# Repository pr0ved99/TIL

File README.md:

# TIL (Today I Learned)
"**2026년 상반기 목표**: AI 의존도를 낮추고 데이터시트 기반의 기술 자립을 이룬다.
(Current Status: Zero to One)"

<div align="center">
  <h3>🚀 Lee YeongHyeon's Tech Archive</h3>
  <p>삼성 청년 SW 아카데미(SSAFY) 임베디드 로봇 트랙에서 공부한 기록입니다.</p>
</div>

<div align="center">

</div>

---

## 📂 Category & Contents
공부한 지식들을 체계적으로 분류하여 관리합니다.

| 카테고리 | 상세 내용 |
| :--- | :--- |
| **💻 Language** | C, C++, Python 핵심 문법 및 고급 기법 |
| **🔌 Embedded** | [STM32(NUCLEO-F446RE)](./Embedded/STM32), [CAN](./Embedded/STM32/CAN), [FreeRTOS](./Embedded/STM32/RTOS), Raspberry Pi 5, Linux 환경 설정 |
| **🤖 Robotics** | [ROS 2 Humble](./Robotics/ROS2), [VSLAM](./Robotics/VSLAM), SLAM, Kinematics, URDF 모델링 |
| **🧠 CS 기초** | Git 컨벤션, 네트워크, OS 원리 |

---

## 📝 Algorithm Study
알고리즘 문제 풀이와 구현 연습은 전용 저장소에서 더욱 밀도 있게 관리하고 있습니다.

> **[Daily Algorithm Repository 바로가기](https://github.com/pr0ved99/daily-algorithm)** > *이곳(TIL)에는 핵심 알고리즘 이론과 오답 노트만 기록합니다.*

---

## 📊 GitHub Stats
<div align="center">

</div>

---

## 💡 My Principles
- **매일 조금씩이라도 기록하기**: 망각하기 전에 내 언어로 정리한다.
- **Why에 집중하기**: 단순 코드가 아닌, 동작 원리와 이유를 파헤친다.
- **공유의 가치**: 누군가에게 도움이 될 수 있는 퀄리티로 작성한다.

<div align="center">
  <p>Copyright © 2026 Lee YeongHyeon. All rights reserved.</p>
</div>

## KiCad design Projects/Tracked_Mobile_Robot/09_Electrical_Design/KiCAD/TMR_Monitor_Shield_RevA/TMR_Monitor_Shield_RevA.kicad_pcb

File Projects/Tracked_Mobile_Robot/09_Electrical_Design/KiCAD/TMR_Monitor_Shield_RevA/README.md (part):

# TMR Monitor Shield RevA — 노트북 설계 시작점

**현재 · 2026-11-12:** [기본 경로의 최신 회로도 PDF](exports/TMR_Monitor_Shield_RevA_schematic.pdf)를 현재 저장 회로도에서 다시 생성했다. 40부품과 PWR_FLAG 2개, J7/J8을 포함한 6개 측정 포트가 반영되어 있다. 왼쪽 아래 `04 VOLTAGE INPUTS – TWO CHANNELS` 영역의 위쪽은 J7/VBAT_SENSE, 아래쪽은 J8/VMOTOR_SENSE다. 11/7 게시본과 본문·렌더링이 일치하며 CAD 원본은 변경하지 않았다. [확인 기록](../../../assets/logs/pcb_design/2026-11-12_export_sync/README.md).

11/13에41-1~41-5 자료 및 기본 exports/reports 최신화를 마감한다. 현재 필기/질문 뒤41-6 보호 경로·검증 기준으로 이어간다. 실물/ADC 검증 완료가 아니다. 회로도 변경 뒤에는 위 고정 경로의 PDF도 함께 갱신한다. 날짜별 검토 로그는 당시 기록으로 보존한다. 아래 재개점은 각 날짜의 이력이다.

**현재 재개점 · 2026-11-07:**

전압2채널·공통 제어와PWR_FLAG2개까지 사용자 작성 완료,40부품·활성22net·기존 설정 ERC0/0이다. Codex가 마감 시 오래된 주석/제목란만 갱신했다. [최신 PDF·검증](../../../assets/logs/pcb_design/2026-11-07_cad_closeout/README.md). 다음은 수집·필터 표와 포트·전원 조건표이며 풋프린트/기구·PCB는 그 뒤다. 후보 BOM은40부품으로 갱신했으나 구매/제작 승인은 아니다. 아래는 당시 이력이다.

**현재 재개점 · 2026-11-06:** TPS=U1·TMUX=U2 추가 후 [24부품을6영역으로 재배치](../../../assets/logs/pcb_design/2026-11-06_schematic_layout_review/README.md)했다. 이후 사용자가 배터리측 J7/R7~R11/C5를 배치해 **현재31부품**이다. J7 위100mil·R9/C5 아래300mil 이동을 실제 저장 파일에서 확인했다. [최신 배치 PDF·검토](../../../assets/logs/pcb_design/2026-11-06_voltage_upstream_placement/README.md). 다음은 사용자가 **전단 분압·필터 배선**→모터 공급측/공통→연결 대조/ERC 순으로 진행한다. [설계27 연결표](../../27_Voltage_2Ch_Schematic_Contract_Comparison_2026-11-06_ko.md)를 따른다. 새7부품14핀과 U1/U2의19핀은 미배선이고 모터 공급측 전압 채널·C7/C8은 미추가다. 활성10net·기존 X70개를 유지한다. 이 쉴드의 새ERC/DRC·PCB 편집은 미실행이며 풋프린트/TI 예시 패드 차이는 후속 검토다. 별도로 수행한 MVP RevB 정돈/ERC와 구분한다. [오늘 진행](../../../docs/progress/2026-11-06_progress.md). 아래 다음 작업은 당시 이력이다.

**이전 재개점 · 2026-10-29:** [학습 노트20](../../../07_Embedded_Learning_Notes/01_Concept_Notes/20_KiCad_Current_NTC_Voltage_Simulation_Lab_ko.md) · [설계 판단24](../../24_Monitoring_Input_Simulation_and_Design_Review_2026-10-28_ko.md) · [실습 원본](../Simulation/README.md). 전류 RC AC/TRAN·NTC25/50°C 상당 OP/AC·전압 분압12.6/16V OP와 AC의 사용자 GUI 실습 및 PNG/CSV 저장을 완료했다. 전압 fc404.942Hz·저주파−15.7157dB·차단점−18.7260dB, NTC VDD(CN7-5) 공급 기본안은 실제 쉴드 미반영이다. 기존22부품/미배선32개쉴드와시뮬레이션회로를구분한다. 다음은 **전압 채널 ±0.10V 목표의 저항 공차·VDDA·ADC/보호 누설·보정 오차 예산 → 정상/고장/무전원 보호 조건 → 준비된 실제 쉴드 변경 검토**다. 아래날짜별다음작업은당시이력이다.

**이전 재개점 · 2026-10-27:** [전류 검증 명세22](../../22_Current_Channel_Verification_Spec_2026-10-27_ko.md)와 [온도 검증 명세23](../../23_Temperature_Channel_Verification_Spec_2026-10-27_ko.md)를 작성했다. 전류 입력계4.4mV·온도 입력계1°C를 시험용 기준으로, 비교 경계·보정/독립점·절차·장비 적합성을 구체화했다. RT 표 환산을 시험 기준으로 사용하고 RC는 비교 대상으로 유지한다. 실물 NOT_RUN·제작용 아님. 다음은 NTC 여기/ADC 기준·무전원 보호의 미결과 전압2채널 설계다. 아래 날짜별3-1 재개 표기는 당시 이력이며 반복 지시가 아니다.

**10/27 외부 설계 비교:** [유사 프로젝트 평가](../../21_External_Project_Monitoring_Architecture_Review_2026-10-27_ko.md)에서 Waveshare·ODrive·VESC의 측정 위치/부품/선정 이유를 비교했다. 현 방향은 타당하나 전압2·전원/보호 결정과 한 채널 검증이 필요하다. 기존 후보·CAD·실측 NOT_RUN은 유지하며, 아래3-1 학습 재개에 연결하는 권고다.

**학습 자료 이력 · 2026-10-26 마감:** [학습 목차](../../../07_Embedded_Learning_Notes/01_Concept_Notes/README.md)에 2장 추가 자료와 **3-1~3-4 검증 학습 노트 네 편**을 작성했다. 다음은 3-1부터 함께 읽기와 목표/오차 배분/계기·연결 조건의 미정 검토다. 12kΩ/100nF·14MHz/480cycles·NTC STM 공급 B안은 후보,100Hz·10개 평균은 첫 DC 비교 제안이다. 실물 시험 NOT_RUN, 요구 채택·부품 확정·CAD/BOM/펌웨어 변경 없음. [마감 근거](../../../docs/progress/2026-10-26_progress.md). 아래 날짜별 “다음”은 당시 이력이다.

2026-10-23. **RevA.0 초안 / 회로도·초기 부품 배치 / 미배선 / 제작용 아님**.

**2단계 종합 검토본:** [ADC6채널 연결·측정 기준](../../20_Analog_6Ch_Contract_and_Stage2_Review_2026-10-23_ko.md). PC0/1 전류·PC2/3 온도·PA4/PB0 전압의 포트/핀 순서를 모았다. 전류센서 nonratiometric·NTC VEXC/VDDA 비율·미분압 rail 보호를 구분했다. 구성 검토본 작성 완료이며 승인/실측 PASS는 아니다. 당시 다음 작업이었던 ADC 기준·NTC 여기·무전원 경로 비교/계산은 아래 10/24 검토에 기록했다. 현재 다음 작업은 상단 최신 재개점을 따른다.

**CAN 연결 계약 초안:** [GPIO·커넥터 검토](../../19_CAN_GPIO_and_Connector_Contract_2026-10-23_ko.md). ESP GPIO4 TX/GPIO5 RX와 ESP 가까운 트랜시버 배치를 제안했다. 별도3.3V 전원·논리3선·버스3선,2/3노드 종단 전환을 기록했다. 기존 UART17/18 유지, HG 실물/전원 OFF 보호·커넥터 제품/키는 미확정. 다음은 ADC6채널 포트/기준 계약과2단계 종합 검토다.

**전원 구조 검토안:** [3.3V 공급·조립 검토](../../18_Expansion_3V3_Supply_Structure_and_Assembly_2026-10-23_ko.md). #2 병렬 분기→단일 LDO→센서/CAN 분배와 TO-220급을 우선 제안한다. 출력 오차 포함 발열 사례0.615W, MCP1825S는 ±2.5%로 초기±1% 탐색 조건에 미달하여 미선정. 무전원 역급전·NTC 기준·#2 전체 여유는 OPEN이다. 다음은 ESP GPIO/커넥터 계약이며 CAD/BOM은 유지한다.

**채택한 목표:** STM 센서/구동 집중 + ESP Wi-Fi–CAN 게이트웨이 + 개발용 CANable. 별도 센서 MCU 추가 없음. 두 MCU용 트랜시버와 각 노드의 전원/핀/배치를 검토한다. 최신 확장 전원은 XL4015 #2 AUX5V 병렬 분기 → 별도3.3V 생성안이다. 추가 부하235mA/연속 설계300mA·LDO 손실약0.51~0.59W 계산안을 검토하며 실제 품번·방열·#2 전체 공급 여유는 미확정이다. [전원 예산 계산](../../17_Expansion_Power_Budget_2026-10-23_ko.md).

**현재 작업은3단계 입력 회로 상세 검토다.** NTC와 전류 RC·ADC 획득·수집 주기·평균·보정 후 오차 예산과 검증 학습 자료를 정리했다. 요구 채택·시험 조건 확정과 실측·부품 확정은 남았다.2단계 계약은20번 문서의 검토본이며 아래 CAD의 실제 전원·커넥터 순서는 아직 이전 초안이다.

이번 회차는 노트북만으로 설계 학습 자료를 정리했고 10/26 마감한다. 다음 물리 작업 시각은 지정하지 않았다. NUCLEO-F446RE 상면 확장 쉴드를 검토하며, **현재 CAD에는 전류 2채널·온도 2채널의 센서 부분만 작성되어 있다. 전체 확장 기능을 반영한 설계가 아니다.** 이 보드 완성은 현재 MVP의 새 선행 조건이 아니다.

## 전체 기능 범위 재대조 — 2026-10-23

사용자가 CAN·향후 LiDAR까지 고려하도록 요청했고, **IMU는 기존 만능기판에 이미 자리를 배치했음**을 재확인했다. 센서 4채널만으로 범위를 좁힌 초기 안내를 정정한다. 기존 기판을 유지하면서 아래 기능을 검토하며, 이번 범위 대조로 CAD 회로나 BOM에 부품을 추가한 것은 아니다.

| 기능 | 새 PCB에서의 처리 | 현재 근거·남은 결정 |
| --- | --- | --- |
| 좌우 모터 전류 2채널 | 외부 #5241의 전원·출력 신호 접속, 입력 필터·보호 | PC0/PC1 초안 있음. 모터 전류가 통과하는 센서 주전류 단자·배선은 외부 유지 |
| 좌우 모터 온도 2채널 | 외부 NTC 접속, 분압·필터·보호 | PC2/PC3 초안 있음. 보호·단선 판정·실물 부품 대조 미완료 |
| **K1 전단·후단 전압 2채널** | 분압·필터·보호·측정점 추가 설계 대상 | PA4/PB0 기존 예약. 현재 CAD에는 없음. 상류 `VBAT_PROTECTED_SENSE`와 하류 `MOTOR_VBAT_SAFE_SENSE` 구분 |
| **CAN** | 트랜시버 접속, CANH/CANL/GND 커넥터, 종단 선택·디커플링·보호 검토 | PA12 TX/PA11 RX 예약. 보유 MCU-230 활용 우선 검토; 실제 단자·크기·RS·내장 종단 미확인. 현재 CAD에는 없음 |
| IMU | **기존 만능기판 위치·배선 유지. 새 PCB에 중복 실장하지 않음** | PB8/PB9 I2C, PB1 INT, PC4 RESET 보존. 기존 JDBG 접근·상면 간섭만 검토. 새 IMU 커넥터도 기본 추가 대상이 아님 |
| 로직 전원·유지보수 | 센서와 CAN을 포함한 3.3V 부하 예산, 전원 디커플링·입력 보호·역급전 경로, 전원/신호 시험점 검토 | 기존 XL4015 전원 경계와 USB 전환 정책 유지. 기존 UART/엔코더/제어/SWD/RESET 접근 보존; 모든 신호의 커넥터 중복 추가는 불필요 |
| 향후 LiDAR·상위 컴퓨터 | 모델 선정 전까지 필요한 전원·데이터 연결 조건과 하네스 통로를 미결 항목으로 관리 | 별도 장착이 기존 방향. 공급 전압·정상/기동 전류·USB/UART/Ethernet 등 실제 인터페이스·커넥터가 정해진 뒤 PCB 포함 여부 결정. 지금 레귤레이터·USB 허브·레벨 변환기를 임의로 추가하지 않음 |
| 예비 확장 | 기존 핀 예약과 물리 접근성 보존 | PA6/PA7 추가 ADC 후보, PC5/PC6 선택적 gate/brake 예약. 현재 필수 회로나 확정 커넥터로 승격하지 않음 |

따라서 기존 계획을 합치면 **아날로그 6채널(전류 2 + 온도 2 + 전압 2)과 CAN**이 새 확장 PCB의 주요 검토 범위다. 전단 전압 입력을 배터리 상태 관측에도 활용하는 안이므로 별도 배터리 ADC를 자동으로 더해 7채널로 세지 않는다. 현재 리포 알람의 사용자 보고 검증과 앞으로 구현할 ADC 측정은 별개다.

CANable V2.0 Pro는 보유한 **PC 측 USB-CAN 장치**다. 새 PCB 실장 부품이나 추가 구매 대상으로 세지 않는다. CAN 종단은 물리 버스 양 끝의 120Ω 구성을 기준으로 하되, 보유 모듈의 내장 종단부터 확인해 중복 추가를 피한다. LiDAR 데이터 경로는 해당 모델과 상위 ROS 2 컴퓨터의 연결을 별도로 정하며, CAN 포트가 LiDAR 데이터 포트를 대신한다고 가정하지 않는다.

MDD10A·XL4015·K1·버스바·퓨즈·배터리는 기존 별도 전력 구역을 유지한다. 엔코더 조정부, PWM/DIR 풀다운, E-stop 감지와 ESP32 UART 회로도 기존 기판에 남긴다. 새 PCB의 부품 수와 면적은 이 경계를 기준으로 산정한다.

근거: [전체 확장 배치 검토](../../13_Two_Deck_Perfboard_Expansion_Feasibility_2026-09-30_ko.md), [전압 ADC 공간 검토](../../12_Dual_Rail_ADC_Space_Review_2026-09-30_ko.md), [현재 핀 배정과 IMU 배선 이력](../../../01_System_Architecture/06_MCU_Pin_Allocation_Candidate_ko.md), [CAN 통합 계획·보유 장비](../../../01_System_Architecture/14_CAN_Bus_Integration_Plan_ko.md). 과거 하층 만능기판의 면적 예산은 현재 상면 쉴드의 수용 가능성 증거가 아니므로 새로 배치 검토한다.

## 열 파일과 현재 결과

1. [KiCad 프로젝트](TMR_Monitor_Shield_RevA.kicad_pro)를 연다.
2. [회로도](TMR_Monitor_Shield_RevA.kicad_sch)를 먼저 보고, [PCB](TMR_Monitor_Shield_RevA.kicad_pcb)에서 배치를 확인한다.
3. 편집 없이 확인하려면 [최신 회로도 PDF](exports/TMR_Monitor_Shield_RevA_schematic.pdf)를 사용한다. [PCB 초기 배치 PDF](exports/TMR_Monitor_Shield_RevA_placement.pdf)는 22풋프린트 초안으로, 최신 회로도의 40부품이 모두 반영된 배치도가 아니다.

[부품 후보 CSV](bom_candidates.csv)는 풋프린트 대조용이며 구매·제작 BOM이 아니다.

| 산출물 | 현재 범위 |
| --- | --- |
| 회로도 | Morpho 암 소켓 2개, 외부 측정 커넥터 6개, 저항 16개, 커패시터 8개, IC 2개, 시험점 6개: 총 40부품. PWR_FLAG 2개 별도 |
| PCB | 부품 22개 배치, 구리 배선/영역 0개. 연결선 32개 미배선 |
| ERC | 11/12 새 추출: 40부품 회로도 오류 0/경고 0, 기존 무시 규칙 4개 유지 |
| DRC | 11/12 저장 PCB 검사: 배치 위반 0, 회로도 대조 21건(미반영 부품18 + net 충돌3), 미배선32. **전체 DRC PASS가 아님** |
| 연결 대조 | 11/12 저장 회로도 추출 결과 전체 91net(활성 22개 포함), 11/7 게시본과 동일. 헤더·외부 포트 활성 핀 23개를 대조 |

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
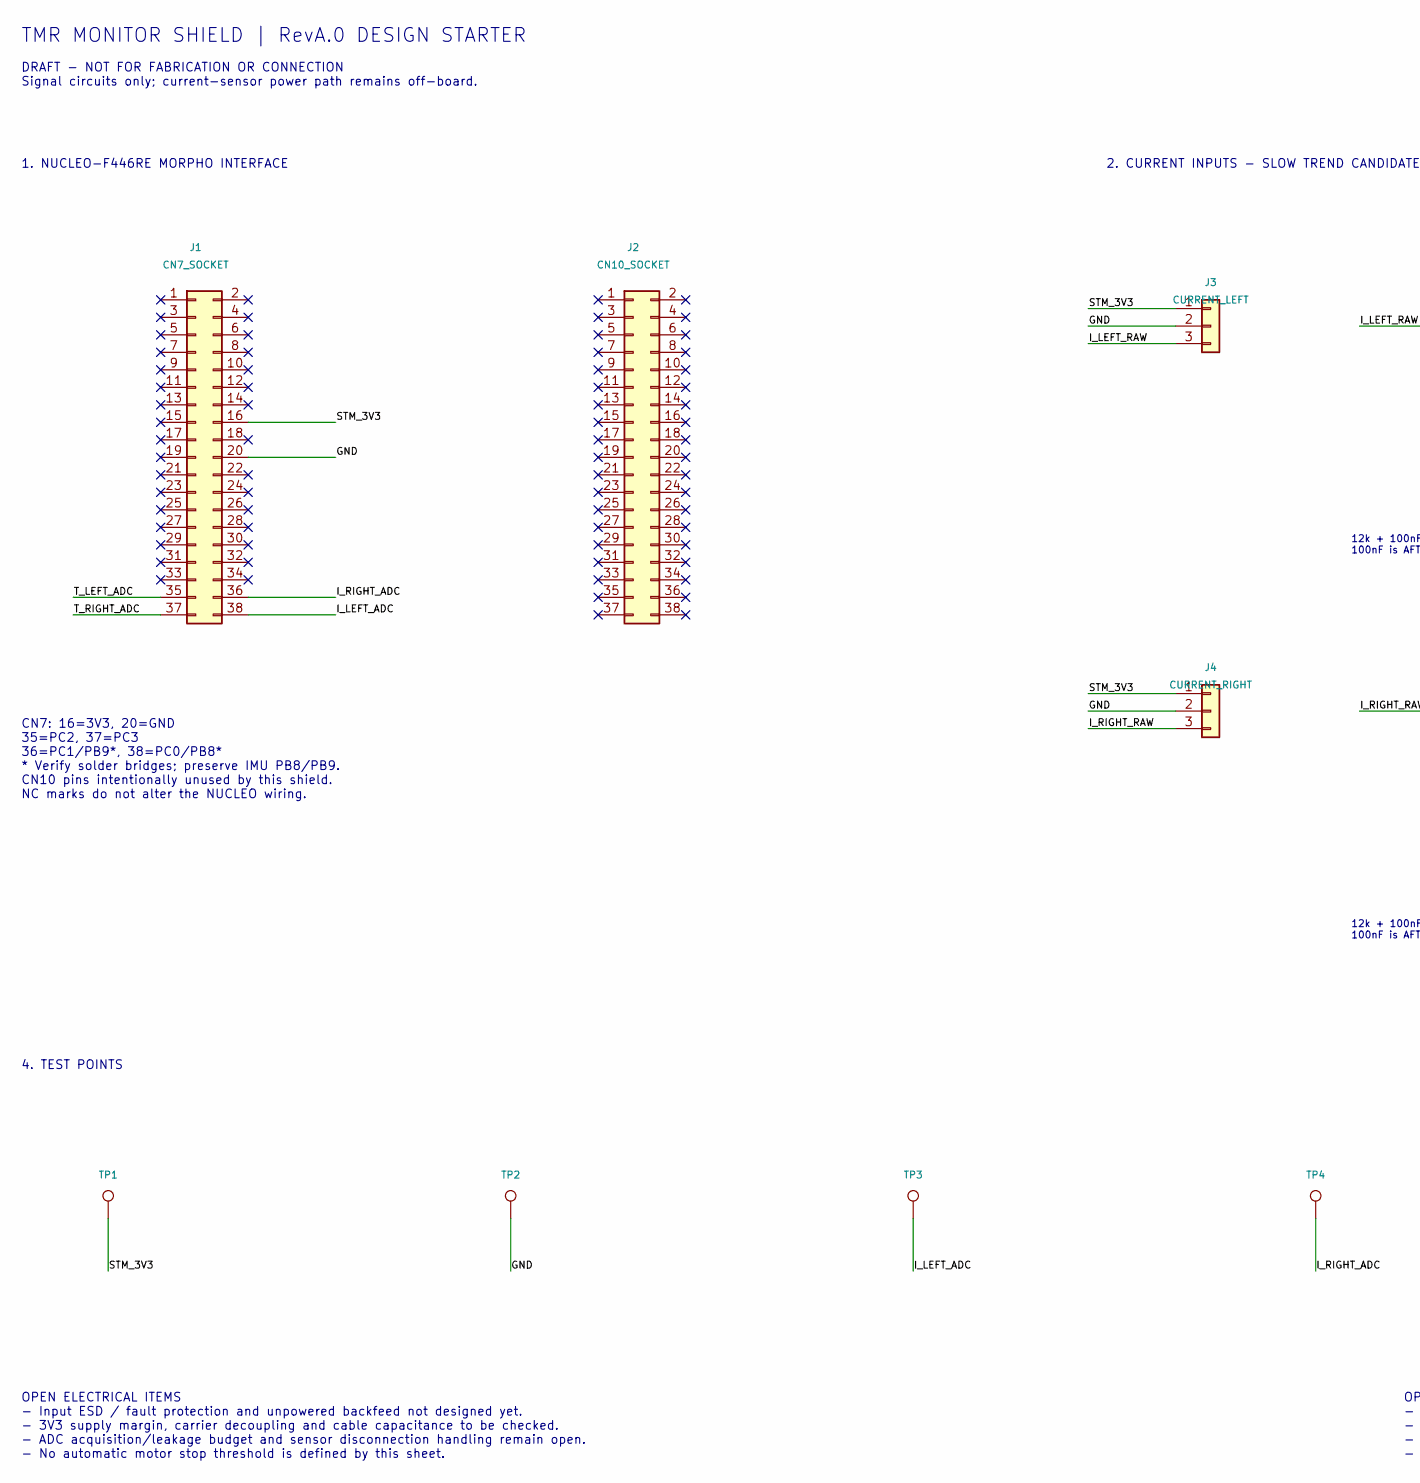
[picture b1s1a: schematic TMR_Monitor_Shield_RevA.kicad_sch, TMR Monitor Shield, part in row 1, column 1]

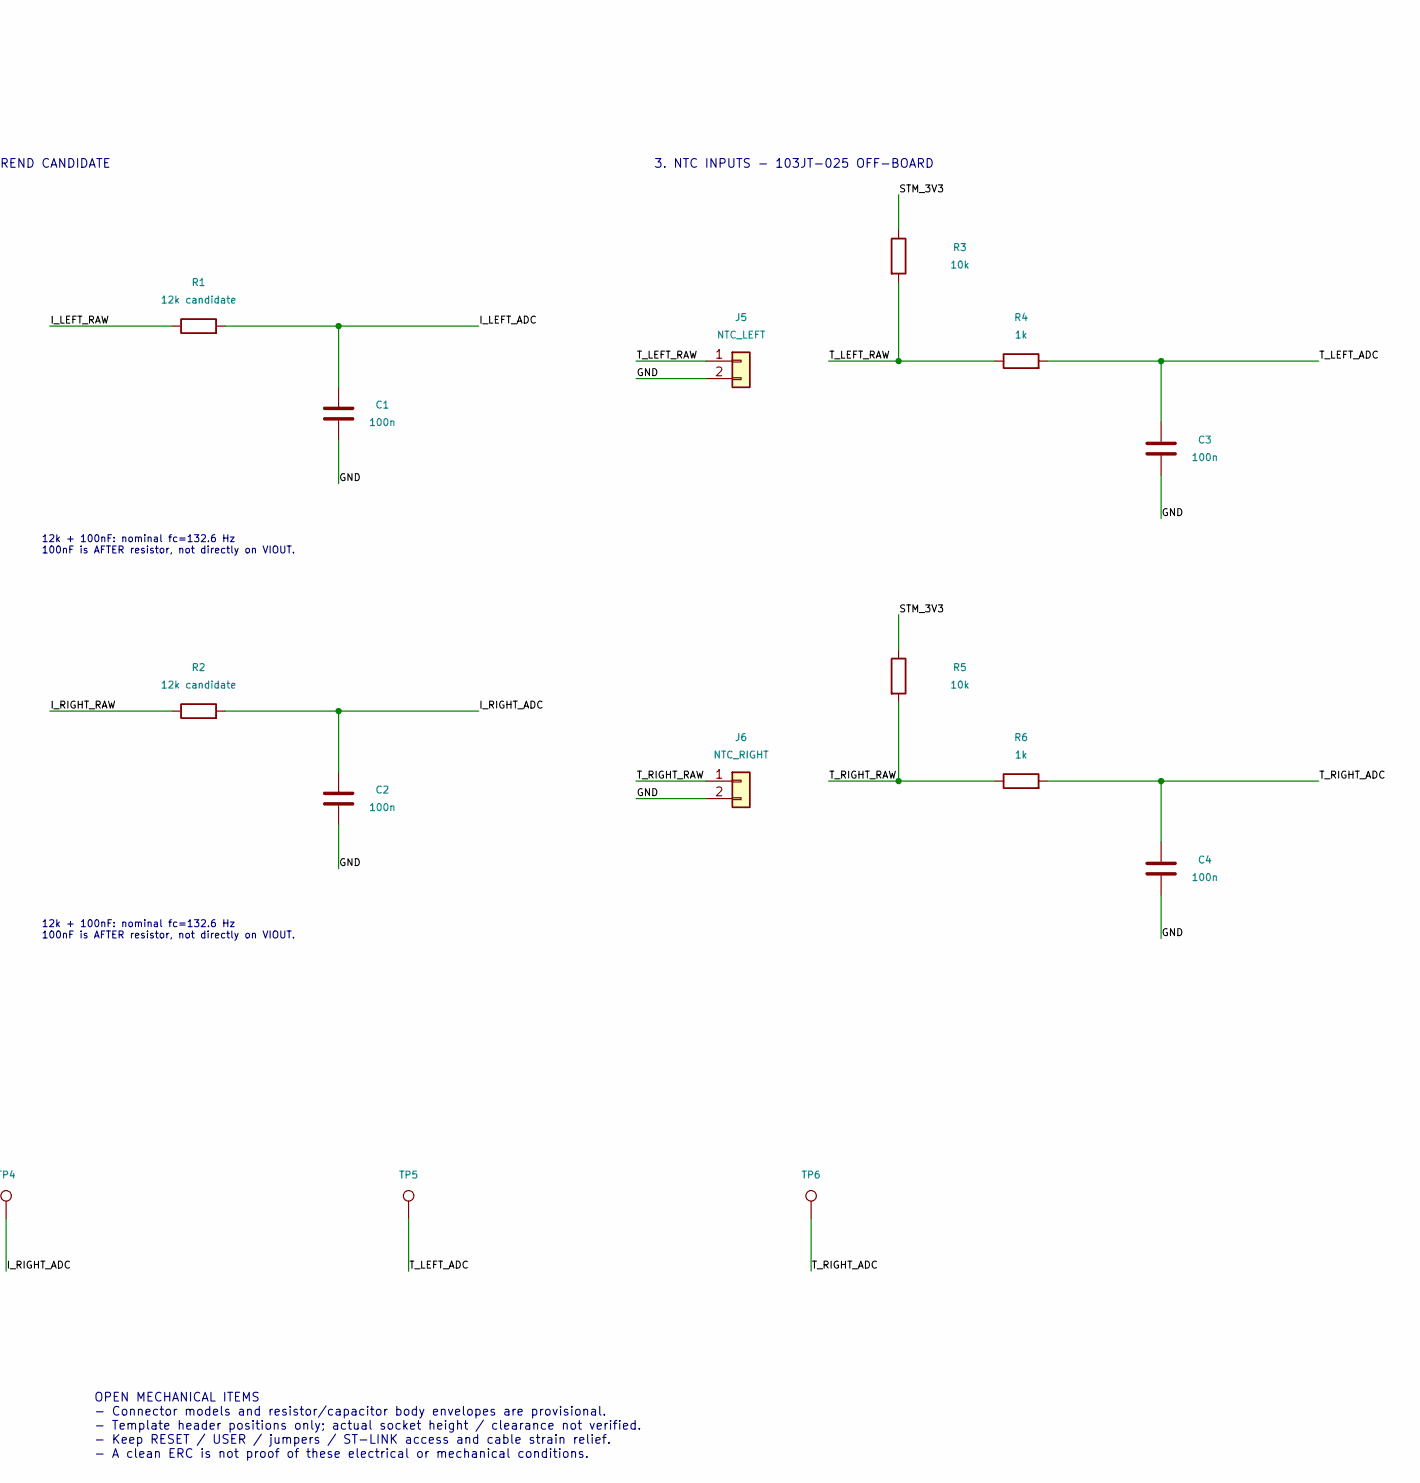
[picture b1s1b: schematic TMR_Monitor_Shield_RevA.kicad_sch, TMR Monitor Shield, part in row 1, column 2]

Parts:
C1, C2, C3, C4: 100n; C_Disc_D5.0mm_W2.5mm_P5.00mm
J1: CN7_SOCKET; PinSocket_2x19_P2.54mm_Vertical
J2: CN10_SOCKET; PinSocket_2x19_P2.54mm_Vertical
J3: CURRENT_LEFT; JST_XH_B3B-XH-A_1x03_P2.50mm_Vertical
J4: CURRENT_RIGHT; JST_XH_B3B-XH-A_1x03_P2.50mm_Vertical
J5: NTC_LEFT; JST_XH_B2B-XH-A_1x02_P2.50mm_Vertical
J6: NTC_RIGHT; JST_XH_B2B-XH-A_1x02_P2.50mm_Vertical
R1, R2: 12k candidate; R_Axial_DIN0207_L6.3mm_D2.5mm_P7.62mm_Horizontal
R3, R5: 10k; R_Axial_DIN0207_L6.3mm_D2.5mm_P7.62mm_Horizontal
R4, R6: 1k; R_Axial_DIN0207_L6.3mm_D2.5mm_P7.62mm_Horizontal
TP1: STM_3V3; TestPoint_THTPad_D1.5mm_Drill0.7mm
TP2: GND; TestPoint_THTPad_D1.5mm_Drill0.7mm
TP3: I_LEFT_ADC; TestPoint_THTPad_D1.5mm_Drill0.7mm
TP4: I_RIGHT_ADC; TestPoint_THTPad_D1.5mm_Drill0.7mm
TP5: T_LEFT_ADC; TestPoint_THTPad_D1.5mm_Drill0.7mm
TP6: T_RIGHT_ADC; TestPoint_THTPad_D1.5mm_Drill0.7mm

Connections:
/GND: C1.2, C2.2, C3.2, C4.2, J1.20, J3.2, J4.2, J5.2, J6.2, TP2.1
/I_LEFT_ADC: C1.1, J1.38, R1.2, TP3.1
/I_LEFT_RAW: J3.3, R1.1
/I_RIGHT_ADC: C2.1, J1.36, R2.2, TP4.1
/I_RIGHT_RAW: J4.3, R2.1
/STM_3V3: J1.16, J3.1, J4.1, R3.1, R5.1, TP1.1
/T_LEFT_ADC: C3.1, J1.35, R4.2, TP5.1
/T_LEFT_RAW: J5.1, R3.2, R4.1
/T_RIGHT_ADC: C4.1, J1.37, R6.2, TP6.1
/T_RIGHT_RAW: J6.1, R5.2, R6.1

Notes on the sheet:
TMR MONITOR SHIELD | RevA.0 DESIGN STARTER
DRAFT - NOT FOR FABRICATION OR CONNECTION Signal circuits only; current-sensor power path remains off-board.
1. NUCLEO-F446RE MORPHO INTERFACE
CN7: 16=3V3, 20=GND 35=PC2, 37=PC3 36=PC1/PB9*, 38=PC0/PB8* * Verify solder bridges; preserve IMU PB8/PB9. CN10 pins intentionally unused by this shield. NC marks do not alter the NUCLEO wiring.
2. CURRENT INPUTS - SLOW TREND CANDIDATE
12k + 100nF: nominal fc=132.6 Hz 100nF is AFTER resistor, not directly on VIOUT.
3. NTC INPUTS - 103JT-025 OFF-BOARD
4. TEST POINTS
OPEN ELECTRICAL ITEMS - Input ESD / fault protection and unpowered backfeed not designed yet. - 3V3 supply margin, carrier decoupling and cable capacitance to be checked. - ADC acquisition/leakage budget and sensor disconnection handling remain open. - No automatic motor stop threshold is defined b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
OPEN MECHANICAL ITEMS - Connector models and resistor/capacitor body envelopes are provisional. - Template header positions only; actual socket height / clearance not verified. - Keep RESET / USER / jumpers / ST-LINK access and cable strain relief. - A clean ERC is not proof of these electrical or 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

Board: 2 copper layers, 22 parts (2 on the bottom side), 10 nets, no tracks yet.

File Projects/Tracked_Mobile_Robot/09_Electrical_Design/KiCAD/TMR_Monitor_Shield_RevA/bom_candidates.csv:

Reference,Value,Footprint_candidate,Status,Notes
J1,CN7_SOCKET,Connector_PinSocket_2.54mm:PinSocket_2x19_P2.54mm_Vertical,CANDIDATE_NOT_PURCHASE_ORDER,Bottom female socket; height and mating geometry to be checked
J2,CN10_SOCKET,Connector_PinSocket_2.54mm:PinSocket_2x19_P2.54mm_Vertical,CANDIDATE_NOT_PURCHASE_ORDER,Bottom female socket; height and mating geometry to be checked
J3,CURRENT_LEFT,Connector_JST:JST_XH_B3B-XH-A_1x03_P2.50mm_Vertical,CANDIDATE_NOT_PURCHASE_ORDER,"JST-XH 3-pin candidate, not purchased or verified; 1=3V3 2=GND 3=VIOUT"
R1,12k candidate,Resistor_THT:R_Axial_DIN0207_L6.3mm_D2.5mm_P7.62mm_Horizontal,VALUE_OWNED_BODY_TOLERANCE_NOT_VERIFIED,Output isolation / RC; value and lead spacing remain provisional
C1,100n,Capacitor_THT:C_Disc_D5.0mm_W2.5mm_P5.00mm,PART_PURCHASED_BODY_FOOTPRINT_NOT_VERIFIED,Vishay K104K15X7RF53H5 purchased; generic body envelope remains provisional
J4,CURRENT_RIGHT,Connector_JST:JST_XH_B3B-XH-A_1x03_P2.50mm_Vertical,CANDIDATE_NOT_PURCHASE_ORDER,"JST-XH 3-pin candidate, not purchased or verified; 1=3V3 2=GND 3=VIOUT"
R2,12k candidate,Resistor_THT:R_Axial_DIN0207_L6.3mm_D2.5mm_P7.62mm_Horizontal,VALUE_OWNED_BODY_TOLERANCE_NOT_VERIFIED,Output isolation / RC; value and lead spacing remain provisional
C2,100n,Capacitor_THT:C_Disc_D5.0mm_W2.5mm_P5.00mm,PART_PURCHASED_BODY_FOOTPRINT_NOT_VERIFIED,Vishay K104K15X7RF53H5 purchased; generic body envelope remains provisional
J5,NTC_LEFT,Connector_JST:JST_XH_B2B-XH-A_1x02_P2.50mm_Vertical,CANDIDATE_NOT_PURCHASE_ORDER,JST-XH 2-pin candidate; 1=NTC node 2=GND; external 103JT-025
R3,10k,Resistor_THT:R_Axial_DIN0207_L6.3mm_D2.5mm_P7.62mm_Horizontal,VALUE_OWNED_BODY_TOLERANCE_NOT_VERIFIED,NTC divider; actual resistance/tolerance and body size unconfirmed
R4,1k,Resistor_THT:R_Axial_DIN0207_L6.3mm_D2.5mm_P7.62mm_Horizontal,VALUE_OWNED_BODY_TOLERANCE_NOT_VERIFIED,Draft component
C3,100n,Capacitor_THT:C_Disc_D5.0mm_W2.5mm_P5.00mm,PART_PURCHASED_BODY_FOOTPRINT_NOT_VERIFIED,Vishay K104K15X7RF53H5 purchased; generic body envelope remains provisional
J6,NTC_RIGHT,Connector_JST:JST_XH_B2B-XH-A_1x02_P2.50mm_Vertical,CANDIDATE_NOT_PURCHASE_ORDER,JST-XH 2-pin candidate; 1=NTC node 2=GND; external 103JT-025
R5,10k,Resistor_THT:R_Axial_DIN0207_L6.3mm_D2.5mm_P7.62mm_Horizontal,VALUE_OWNED_BODY_TOLERANCE_NOT_VERIFIED,NTC divider; actual resistance/tolerance and body size unconfirmed
R6,1k,Resistor_THT:R_Axial_DIN0207_L6.3mm_D2.5mm_P7.62mm_Horizontal,VALUE_OWNED_BODY_TOLERANCE_NOT_VERIFIED,Draft component
C4,100n,Capacitor_THT:C_Disc_D5.0mm_W2.5mm_P5.00mm,PART_PURCHASED_BODY_FOOTPRINT_NOT_VERIFIED,Vishay K104K15X7RF53H5 purchased; generic body envelope remains provisional
TP1,STM_3V3,TestPoint:TestPoint_THTPad_D1.5mm_Drill0.7mm,BARE_PCB_TEST_PAD,Draft component
TP2,GND,TestPoint:TestPoint_THTPad_D1.5mm_Drill0.7mm,BARE_PCB_TEST_PAD,Draft component
TP3,I_LEFT_ADC,TestPoint:TestPoint_THTPad_D1.5mm_Drill0.7mm,BARE_PCB_TEST_PAD,Draft component
TP4,I_RIGHT_ADC,TestPoint:TestPoint_THTPad_D1.5mm_Drill0.7mm,BARE_PCB_TEST_PAD,Draft component
TP5,T_LEFT_ADC,TestPoint:TestPoint_THTPad_D1.5mm_Drill0.7mm,BARE_PCB_TEST_PAD,Draft component
TP6,T_RIGHT_ADC,TestPoint:TestPoint_THTPad_D1.5mm_Drill0.7mm,BARE_PCB_TEST_PAD,Draft component

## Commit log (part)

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2026-01-03 docs: 리드미 작성 및 깃 협업 가이드 추가
2026-01-03 Fix link to Daily Algorithm Repository
2026-01-03 Git 기초 지식을 공부 / v1
2026-01-03 docs: Git 기초 가이드 어투 수정 및 TIL 스타일로 리팩토링
2026-01-03 style: fix typos
2026-01-03 docs: 커밋 컨벤션(Conventional Commits) 가이드 추가
2026-01-03 fix: 중첩되는 내용의 파일 정리
2026-01-03 docs: 협업에 필요한 공부 업로드
2026-01-03 fix: reconstruction
2026-01-03 fix: 자잘한 오타 수정...
    브렌치도 만들어서 수정했지만 main과 merge하면 보이는 오타들...
    진짜 merge...
2026-01-03 Revise README structure and add new content
    Updated README to include new sections and images.
2026-01-04 docs: 프로젝트 제안서 초안과 기타 마크다운 파일 생성
2026-01-05 fix: 명세서에 부합하는 제안서로 수정 1
2026-01-06 Refine team roles and responsibilities in proposal
2026-01-17 프로젝트 이름 최종 수정
2026-01-17 docs: 로봇 조립도, 폭파도 및 층별 도면 프리뷰 이미지 추가
2026-01-17 docs: 하드웨어 설계 개요 및 조립/폭파도 이미지 추가
2026-01-17 docs: 6구 퓨즈박스 중심 전원 분배 계통 정의
2026-01-17 docs: 구매 목록 시트 기반 하드웨어 BOM 최신화
2026-01-17 docs: 부품 명세(BOM) 최신화 및 상세 핀 맵(PinMapping) 추가
2026-02-22 Delete Project/PET_Ner directory
    올바른 Direction으로 이전 예정
2026-02-22 docs: Add Ubuntu STM32CubeIDE 2.0 & CubeMX installation guide
2026-02-22 docs: Update README, .gitignore and Gitignore_Setup.md for STM32 environment
2026-02-22 refactor: Reorganize STM32 docs into Theory and Practice & rename Blinky tutorial
2026-02-22 docs: Add HAL vs LL comparison & new tutorial with assets directory
2026-02-22 docs: Rename theory docs with numeric prefixes & add F446RE hardware overview
2026-02-22 docs: Fix image extension for usb cable from png to jpeg
2026-02-22 docs: Format hardware overview with tables for better readability
2026-02-22 docs: Add LL Hybrid Blinky tutorial in Practice folder
2026-02-22 docs: Add EXTI push button interrupt tutorial in Practice folder
2026-02-22 docs: Rewrite PWM tutorial in TIL (declarative) style
2026-02-22 feat: Add F446RE EXTI and PWM project files
2026-02-22 chore: Set up Reinforcement Learning directory structure
2026-02-22 chore: Set up Jira directory structure
2026-02-22 feat: Add STM32 F446RE PWM tutorial markdown file.
2026-02-22 feat: Initialize Python virtual environment and install project dependencies.
2026-02-22 docs: Translate README.md to Korean
2026-04-08 add vslam study directory structure
2026-04-08 add d435i vslam implementation plan
2026-04-08 add jetson orin nano docker study docs
2026-04-09 docs: add outdoor trash robot development roadmaps
2026-04-11 docs: reorganize vslam docs and daily logs
2026-04-11 feat: add d435i debugging and mapping scripts
2026-04-11 docs: add d435i evidence assets
2026-04-11 fix: relax rtabmap rgbd odometry startup settings
2026-04-11 docs: explain viewer and rtabmap realtime gap
2026-04-11 docs: add odom comparison and update rtabmap status
2026-04-11 docs: add imu axis notes and refresh progress
2026-04-13 docs: add pre-arrival fusion plan and model exports
2026-04-13 Update VSLAM RTAB-Map workflow and sprint docs
2026-04-14 Add RTAB-Map retest logs and BNO08x placement guide
2026-04-17 Add Jetson VSLAM bring-up docs
2026-04-21 Add Jetson RTAB-Map benchmark assets and templates
2026-04-21 Add BNO08x Jetson bring-up and viewer tools
2026-04-21 Add Jetson Docker RTAB-Map stack and diagnostics
2026-04-21 Update Jetson VSLAM indexes and progress docs
2026-04-23 Add Jetson BNO08x IMU comparison benchmark
2026-04-23 Add trashbot URDF RViz model draft
2026-04-23 Add VSLAM daily index
2026-04-23 Add D435i RTAB-Map VSLAM manual
2026-04-23 Add 2026-04-23 VSLAM CAD preparation log
2026-04-23 Add Jetson Docker VSLAM docs tools and small turtle prep
2026-04-24 feat(vslam): add small turtle urdf sensor prep
2026-04-25 docs: record small turtle urdf planning
2026-04-27 docs: update mari gazebo model progress
2026-04-27 feat: add Mari RViz TF checks and Jetson handoff
2026-04-28 feat(vslam): add Mari Gazebo RTAB-Map baseline
2026-05-01 feat: add Mari Gazebo localization validation
    Add Mari Gazebo sensor, encoder, EKF, RTAB-Map, park-world validation assets and documentation.
2026-05-04 Add Mari Nav2 saved-map navigation workflow
2026-05-05 docs: record Jetson GPS UART troubleshooting
2026-05-07 docs(vslam): record rtabmap multisession db reuse
    Refs S14P31C205-678
    Refs S14P31C205-679
2026-05-11 docs(vslam): record S14P31C205-735 Duri validation
2026-05-13 docs(vslam): record S14P31C205-735-1327 Jira backlog updates
2026-05-13 docs(vslam): record S14P31C205-1282 trash pose projection
2026-05-21 docs(vslam): record Duri autonomy progress
2026-05-21 docs(stm32): add CAN FreeRTOS roadmap notes
2026-05-21 docs(os): add dinosaur book learning notes
2026-05-22 docs(esp32): add ESP32-S3 setup notes
2026-05-22 docs(esp32): record RGB LED practice
2026-05-24 docs(cleanup): record laptop git preservation plan
2026-05-24 docs(cleanup): add laptop migration plan
2026-05-24 docs(cleanup): add google drive upload manifest
2026-06-03 docs(robot): add tracked mobile robot design notes
2026-06-04 docs(robot): add handoff for tracked mobile robot
2026-06-07 docs(ros2): add project learning roadmap
2026-06-07 docs(stm32): add can and rtos learning maps
2026-06-07 docs(robot): update tracked robot architecture
2026-06-08 docs(robot): add MDD10A hardware execution plan
2026-06-13 docs: move CS study notes into TIL
2026-06-21 feat: add tracked robot UART MVP tooling
2026-06-22 docs: refresh tracked robot handoff
2026-06-22 Add STM32 UART MVP firmware and validation evidence
2026-06-27 Implement STM32 UART MVP protocol

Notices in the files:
Projects/Tracked_Mobile_Robot/09_Electrical_Design/KiCAD/TMR_Monitor_Shield_RevA/README.md:
- [템플릿 출처·변경 범위](reports/template_provenance.json): KiCad 배포 템플릿, TiZed (2021), CC0. 설치 템플릿에서 파생된 외곽과 헤더 배치를 사용했다.
